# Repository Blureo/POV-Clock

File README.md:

# POV-Clock
Persistence-of-Vision LED Clock

This is an LED clock that makes use of persistence-of-vision to display time and temperature. The time can be set using the rotary encoder and 2 buttons (there are 3, but one was not used in the current iteration).

-------

This project was made in collaboration with 2 others: Joshua Sevick and Kolby Kriegelstein.

I, Jesse Thompson, was responsible for the PCB design, Real-time Clock (RTC), and implementing the rotary encoder's drivers in the RTC. All group members made their own drivers for the UART, ADC (for temperature), and bar of 16 LED's.

The design is based on the NXP MKL16Z MCU and was programmed in C++ using Keil uVision.

-------

## How to Use:
Time is set to zero by default. To set the time, press the edit button and use the rotary encoder to set hour and minute to desired number (switch between hour and minute mode using the hr/min button. If you experience difficulty seeing the time you are setting the clock to, connect a serial cable to the UART pins, and using an application such as PuTTY with a baud of 9600, you can see the time getting updated as you rotate the encoder. If using a terminal, connect the +5V pin. If using a PC, ***do not*** connect the +5V pin.

To see the time, flick your eyes across the LEDs. Moving one's head does not achieve the desired effect well. 

-------

## Current issues and future fixes
1. Edit mode spontaneously turns on despite the button not being pressed. Unsure at this time as to why this occurs. **Fix**: edit mode will only be on if the button is continuously pressed down.

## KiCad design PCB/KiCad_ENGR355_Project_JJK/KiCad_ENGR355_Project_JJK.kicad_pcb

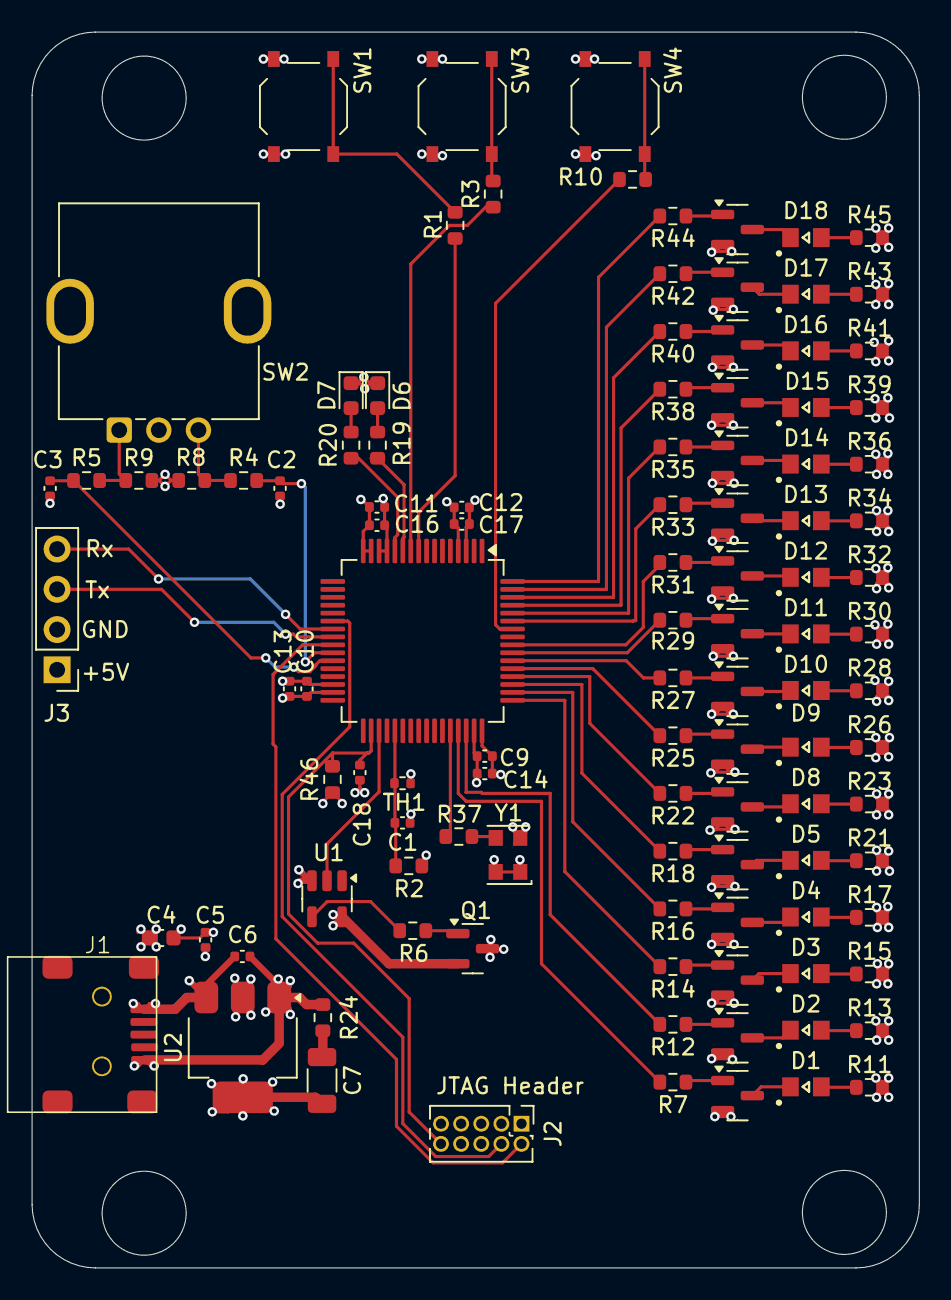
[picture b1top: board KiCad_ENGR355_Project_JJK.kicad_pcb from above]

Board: 4 copper layers, 56.0 x 78.0 mm, 113 parts (0 on the bottom side), 94 nets.

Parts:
C1, C2, C3, C5, C9, C10, C16, C17: 0.1u; C_0402_1005Metric
C4: 4.7u; C_0603_1608Metric
C6, C11, C12, C13, C14, C18: 1u; C_0402_1005Metric
C7: 22u; C_1206_3216Metric
D1, D2, D3, D4, D5, D8, D9, D10, D11, D12, D13, D14, D15, D16, D17, D18: LED_Honglitronic_HL-PSC-2012
D6, D7: LED; LED_0603_1608Metric
H1, H2, H3, H4: MountingHole; MountingHole_5.3mm_M5
J1: USB_B_Mini; UX-144S-ACP5
J2: JTAG SWD; PinHeader_2x05_P1.27mm_Vertical
J3: Conn_01x04; PinHeader_1x04_P2.54mm_Vertical
Q1: AO3401A; SOT-23
Q2, Q3, Q4, Q5, Q6, Q7, Q8, Q9, Q10, Q11, Q12, Q13, Q14, Q15, Q16, Q17: AO3400A; SOT-23
R1, R3, R10: 330; R_0603_1608Metric
R2: 100k; R_0603_1608Metric
R4, R5, R8, R9: 4.7k; R_0603_1608Metric
R6: 47; R_0603_1608Metric
R7, R11, R12, R13, R14, R15, R16, R17, R18, R19, R20, R21, R22, R23, R25, R26, R27, R28, R29, R30, R31, R32, R33, R34, R35, R36, R37, R38, R39, R40, R41, R42, R43, R44, R45: 100; R_0603_1608Metric
R24: 1; R_0603_1608Metric
R46: 10k; R_0603_1608Metric
SW1, SW3, SW4: SW_Push; SW_Push_1P1T_XKB_TS-1187A
SW2: RotaryEncoder; RotaryEncoder_Bourns_Vertical_PEC12R-3x17F-Nxxxx
TH1: 100k; R_0402_1005Metric
U1: SN74LV1T34DBV; SOT-23-5
U2: AMS1117-3.3; SOT-223-3_TabPin2
U3: MKL16Z128VLH4; LQFP-64_10x10mm_P0.5mm
Y1: XO32; Oscillator_SMD_EuroQuartz_XO32-4Pin_3.2x2.5mm

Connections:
+3.3V: C7.1, C9.2, C10.2, C11.1, C12.1, C13.1, C14.1, C16.2, C17.2, J2.1, R2.2, R8.2, R9.2, R46.1, U2.2 (VO), U3.3 (VDD), U3.13 (VDDA), U3.14 (VREFH), U3.30 (VDD), U3.48 (VDD), Y1.1 (EN), Y1.4 (V+)
+5V: C4.2, C5.2, C6.1, J1.1 (VBUS), J3.1, Q1.2 (S), U1.5 (VCC), U2.3 (VI)
GND: C1.1, C2.1, C3.1, C4.1, C5.1, C6.2, C9.1, C10.1, C11.2, C12.2, C13.2, C14.2, C16.1, C17.1, C18.2, D6.1 (K), D7.1 (K), J1.5 (GND), J2.3, J2.5, J2.9, J3.2, Q2.2 (S), Q3.2 (S), Q4.2 (S), Q5.2 (S), Q6.2 (S), Q7.2 (S), Q8.2 (S), Q9.2 (S), Q10.2 (S), Q11.2 (S), Q12.2 (S), Q13.2 (S), Q14.2 (S), Q15.2 (S), Q16.2 (S), Q17.2 (S), R24.2, SW1.1, SW2.C, SW3.1, SW4.1, TH1.2, U1.3 (GND), U2.1 (GND), U3.4 (VSS), U3.15 (VREFL), U3.16 (VSSA), U3.31 (VSS), U3.47 (VSS), Y1.2 (GND)
unnamed: C7.2, R24.1
unnamed: D1.2 (A), R11.1
unnamed: D1.1 (K), Q2.3 (D)
unnamed: D2.2 (A), R13.1
unnamed: D2.1 (K), Q3.3 (D)
unnamed: D3.2 (A), R15.1
unnamed: D3.1 (K), Q4.3 (D)
unnamed: D4.2 (A), R17.1
unnamed: D4.1 (K), Q5.3 (D)
unnamed: D5.2 (A), R21.1
unnamed: D5.1 (K), Q6.3 (D)
unnamed: D6.2 (A), R19.2
unnamed: D7.2 (A), R20.2
unnamed: D8.2 (A), R23.1
unnamed: D8.1 (K), Q7.3 (D)
unnamed: D9.2 (A), R26.1
unnamed: D9.1 (K), Q8.3 (D)
unnamed: D10.2 (A), R28.1
unnamed: D10.1 (K), Q9.3 (D)
unnamed: D11.2 (A), R30.1
unnamed: D11.1 (K), Q10.3 (D)
unnamed: D12.2 (A), R32.1
unnamed: D12.1 (K), Q11.3 (D)
unnamed: D13.2 (A), R34.1
unnamed: D13.1 (K), Q12.3 (D)
unnamed: D14.2 (A), R36.1
unnamed: D14.1 (K), Q13.3 (D)
unnamed: D15.2 (A), R39.1
unnamed: D15.1 (K), Q14.3 (D)
unnamed: D16.2 (A), R41.1
unnamed: D16.1 (K), Q15.3 (D)
unnamed: D17.2 (A), R43.1
unnamed: D17.1 (K), Q16.3 (D)
unnamed: D18.2 (A), R45.1
unnamed: D18.1 (K), Q17.3 (D)
unnamed: J3.3, U3.24 (PTA2)
unnamed: J3.4, U3.23 (PTA1)
unnamed: Q1.3 (D), R11.2, R13.2, R15.2, R17.2, R21.2, R23.2, R26.2, R28.2, R30.2, R32.2, R34.2, R36.2, R39.2, R41.2, R43.2, R45.2
unnamed: Q1.1 (G), R6.1
unnamed: Q2.1 (G), R7.1
unnamed: Q3.1 (G), R12.1
unnamed: Q4.1 (G), R14.1
unnamed: Q5.1 (G), R16.1
unnamed: Q6.1 (G), R18.1
unnamed: Q7.1 (G), R22.1
unnamed: Q8.1 (G), R25.1
unnamed: Q9.1 (G), R27.1
unnamed: Q10.1 (G), R29.1
unnamed: Q11.1 (G), R31.1
unnamed: Q12.1 (G), R33.1
unnamed: Q13.1 (G), R35.1
unnamed: Q14.1 (G), R38.1
unnamed: Q15.1 (G), R40.1
unnamed: Q16.1 (G), R42.1
unnamed: Q17.1 (G), R44.1
unnamed: R1.1, SW1.2
unnamed: R3.1, SW3.2
unnamed: R4.1, R8.1, SW2.B
unnamed: R5.2, R9.1, SW2.A
unnamed: R10.1, SW4.2
unnamed: R6.2, U1.4 (Y)
unnamed: R37.2, U3.44 (PTC1/LLWU_P6/RTC_CLKIN)
unnamed: R37.1, Y1.3 (OUT)
PTA0: J2.4, U3.22 (PTA0)
PTA3: J2.2, U3.25 (PTA3)
PTA4: C2.2, R4.2, U3.26 (PTA4)
PTA5: C3.2, R5.1, U3.27 (PTA5)
PTA20: C18.1, J2.10, R46.2, U3.34 (PTA20)
PTB0: U1.2 (A), U3.35 (PTB0/LLWU_P5)
PTB2: C1.2, R2.1, TH1.1, U3.37 (PTB2)
PTC2: R7.2, U3.45 (PTC2)
PTC3: R12.2, U3.46 (PTC3/LLWU_P7)
PTC4: R14.2, U3.49 (PTC4/LLWU_P8)
PTC5: R16.2, U3.50 (PTC5/LLWU_P9)
PTC6: R18.2, U3.51 (PTC6/LLWU_P10)
PTC7: R22.2, U3.52 (PTC7)
PTC8: R25.2, U3.53 (PTC8)
PTC9: R27.2, U3.54 (PTC9)
PTC10: R29.2, U3.55 (PTC10)
PTC11: R31.2, U3.56 (PTC11)
PTD1: R10.2, U3.58 (PTD1)
PTD2: R33.2, U3.59 (PTD2)
PTD3: R35.2, U3.60 (PTD3)
PTD4: R38.2, U3.61 (PTD4/LLWU_P14)
PTD5: R40.2, U3.62 (PTD5)
PTD6: R42.2, U3.63 (PTD6/LLWU_P15)
PTD7: R44.2, U3.64 (PTD7)
PTE20: R1.2, U3.9 (PTE20)
PTE21: R3.2, U3.10 (PTE21)
PTE22: R19.1, U3.11 (PTE22)
PTE23: R20.1, U3.12 (PTE23)

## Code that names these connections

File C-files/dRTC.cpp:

#include "dRTC.h"
#include "DRot.h"
#include <stdio.h>
#include <MKL16Z4.h>
#include "DLED.h"

dRTC::dRTC() // constructor
{
	edit = false; // edit mode off by default
	timeTypeEdit = true; // hour mode by default
	userHour = 0;
	userMinute = 0;
}

void dRTC::Init()
{
	SIM->SCGC5 |= SIM_SCGC5_PORTD_MASK; // enable PORTD for buttons
	SIM->SCGC5 |= SIM_SCGC5_PORTE_MASK; // enable PORTE for buttons
	SIM->SCGC5 |= SIM_SCGC5_PORTC_MASK; // enable PTC1
	SIM->SCGC6 |= SIM_SCGC6_RTC_MASK; // enabling software access and interrupts for RTC
	SIM->SOPT1 = (SIM->SOPT1 & ~SIM_SOPT1_OSC32KSEL_MASK) | SIM_SOPT1_OSC32KSEL(0b10); // selecting RTC_CLKIN
	
	
	PORTC->PCR[1] = (PORTC->PCR[1] & ~PORT_PCR_MUX_MASK) | PORT_PCR_MUX(1); // selecting alt 1
	PORTD->PCR[1] = (PORTD->PCR[1] & ~(PORT_PCR_MUX_MASK | PORT_PCR_PS_MASK| PORT_PCR_IRQC_MASK)) | PORT_PCR_MUX(0b001) | PORT_PCR_IRQC(0b1010)  | PORT_PCR_PS_MASK; // select GPIO functionality on PTD1, enable pull-up/down, select pull-down
	PORTE->PCR[20] = (PORTE->PCR[20] & ~(PORT_PCR_MUX_MASK | PORT_PCR_PS_MASK)) | PORT_PCR_MUX(0b001) | PORT_PCR_PE_MASK |  PORT_PCR_PS_MASK; // select GPIO functionality on PTE20, enable pull-up/down, select pull-down
	PORTE->PCR[21] = (PORTE->PCR[21] & ~(PORT_PCR_MUX_MASK | PORT_PCR_PS_MASK)) | PORT_PCR_MUX(0b001) | PORT_PCR_PE_MASK | PORT_PCR_PS_MASK; // select GPIO functionality on PTE21, enable pull-up/down, select pull-down
	
	PORTE->PCR[23] = (PORTE->PCR[22] &~PORT_PCR_MUX_MASK)|PORT_PCR_MUX(1);	// LED that flashes every second 
	PORTE->PCR[22] = (PORTE->PCR[23] &~PORT_PCR_MUX_MASK)|PORT_PCR_MUX(1);	// LED that is turned on and off during set time
	PTE->PDDR |= 0xC00000;
	// Default is input, so no need to set PDDR for buttons
	
	RTC->IER |= RTC_IER_TSIE_MASK; // enable time second interrupts
	
	RTC->TSR = 0; // set timer to initial value (zero or other)
	RTC->SR |= RTC_SR_TCE_MASK; // enable timer
	
	NVIC_EnableIRQ(RTC_Seconds_IRQn);
	NVIC_EnableIRQ(PORTC_PORTD_IRQn);
}


// setTime needs to be a loop which is active once edit button is pressed and until its pressed again
// while its high it constantly updates class variable time according to user inputs
void dRTC::editTime()
{
	userHour = RTC->TSR/3600;
	userMinute = (RTC->TSR % 3600) / 60;
	
	PTE->PSOR |= 0x800000;
	g_DLED.LEDBrightness(20);
	while (edit)
	{
		if (timeTypeEdit) // edit hours
		{
			userHour = g_DRot.Get(); // set userHour to encoder value constantly until mode is changed or edit mode is exited
			if (userHour > 23)
				userHour = 23;
		}
		else // edit minute
		{
			userMinute = g_DRot.Get(); // set userMinute to encoder value constantly until mode is changed or edit mode is exited
		}
		
		time = (userHour*100) + userMinute; // set time variable so clockface can read it and send it while editing
	} // while (edit)
	RTC->SR &= ~RTC_SR_TCE_MASK; // disable timer
	RTC->TSR = userHour*3600 + userMinute*60; // update RTC with new time
	RTC->SR |= RTC_SR_TCE_MASK; // enable timer
	PTE->PCOR |= 0x800000;
	g_DLED.LEDBrightness(100);
} // function

int dRTC::getTime()
{
	int temp = RTC->TSR;
	int hour;
	int minute;
	
	if (edit)
		return time;
	else
	{
		hour = temp/3600; // set hours
		minute = (temp % 3600) / 60; // set minutes
		return (100*hour + minute);
	}
}

int dRTC::getRTC()
{
	return RTC->TSR;
}

void dRTC::editToggle()
{
	g_RTC.edit = !g_RTC.edit;
}


void dRTC::timeTypeToggle()
{
	timeTypeEdit = !timeTypeEdit;
}

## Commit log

2025-04-01 Added PCB files
2025-04-01 Added Source Code
